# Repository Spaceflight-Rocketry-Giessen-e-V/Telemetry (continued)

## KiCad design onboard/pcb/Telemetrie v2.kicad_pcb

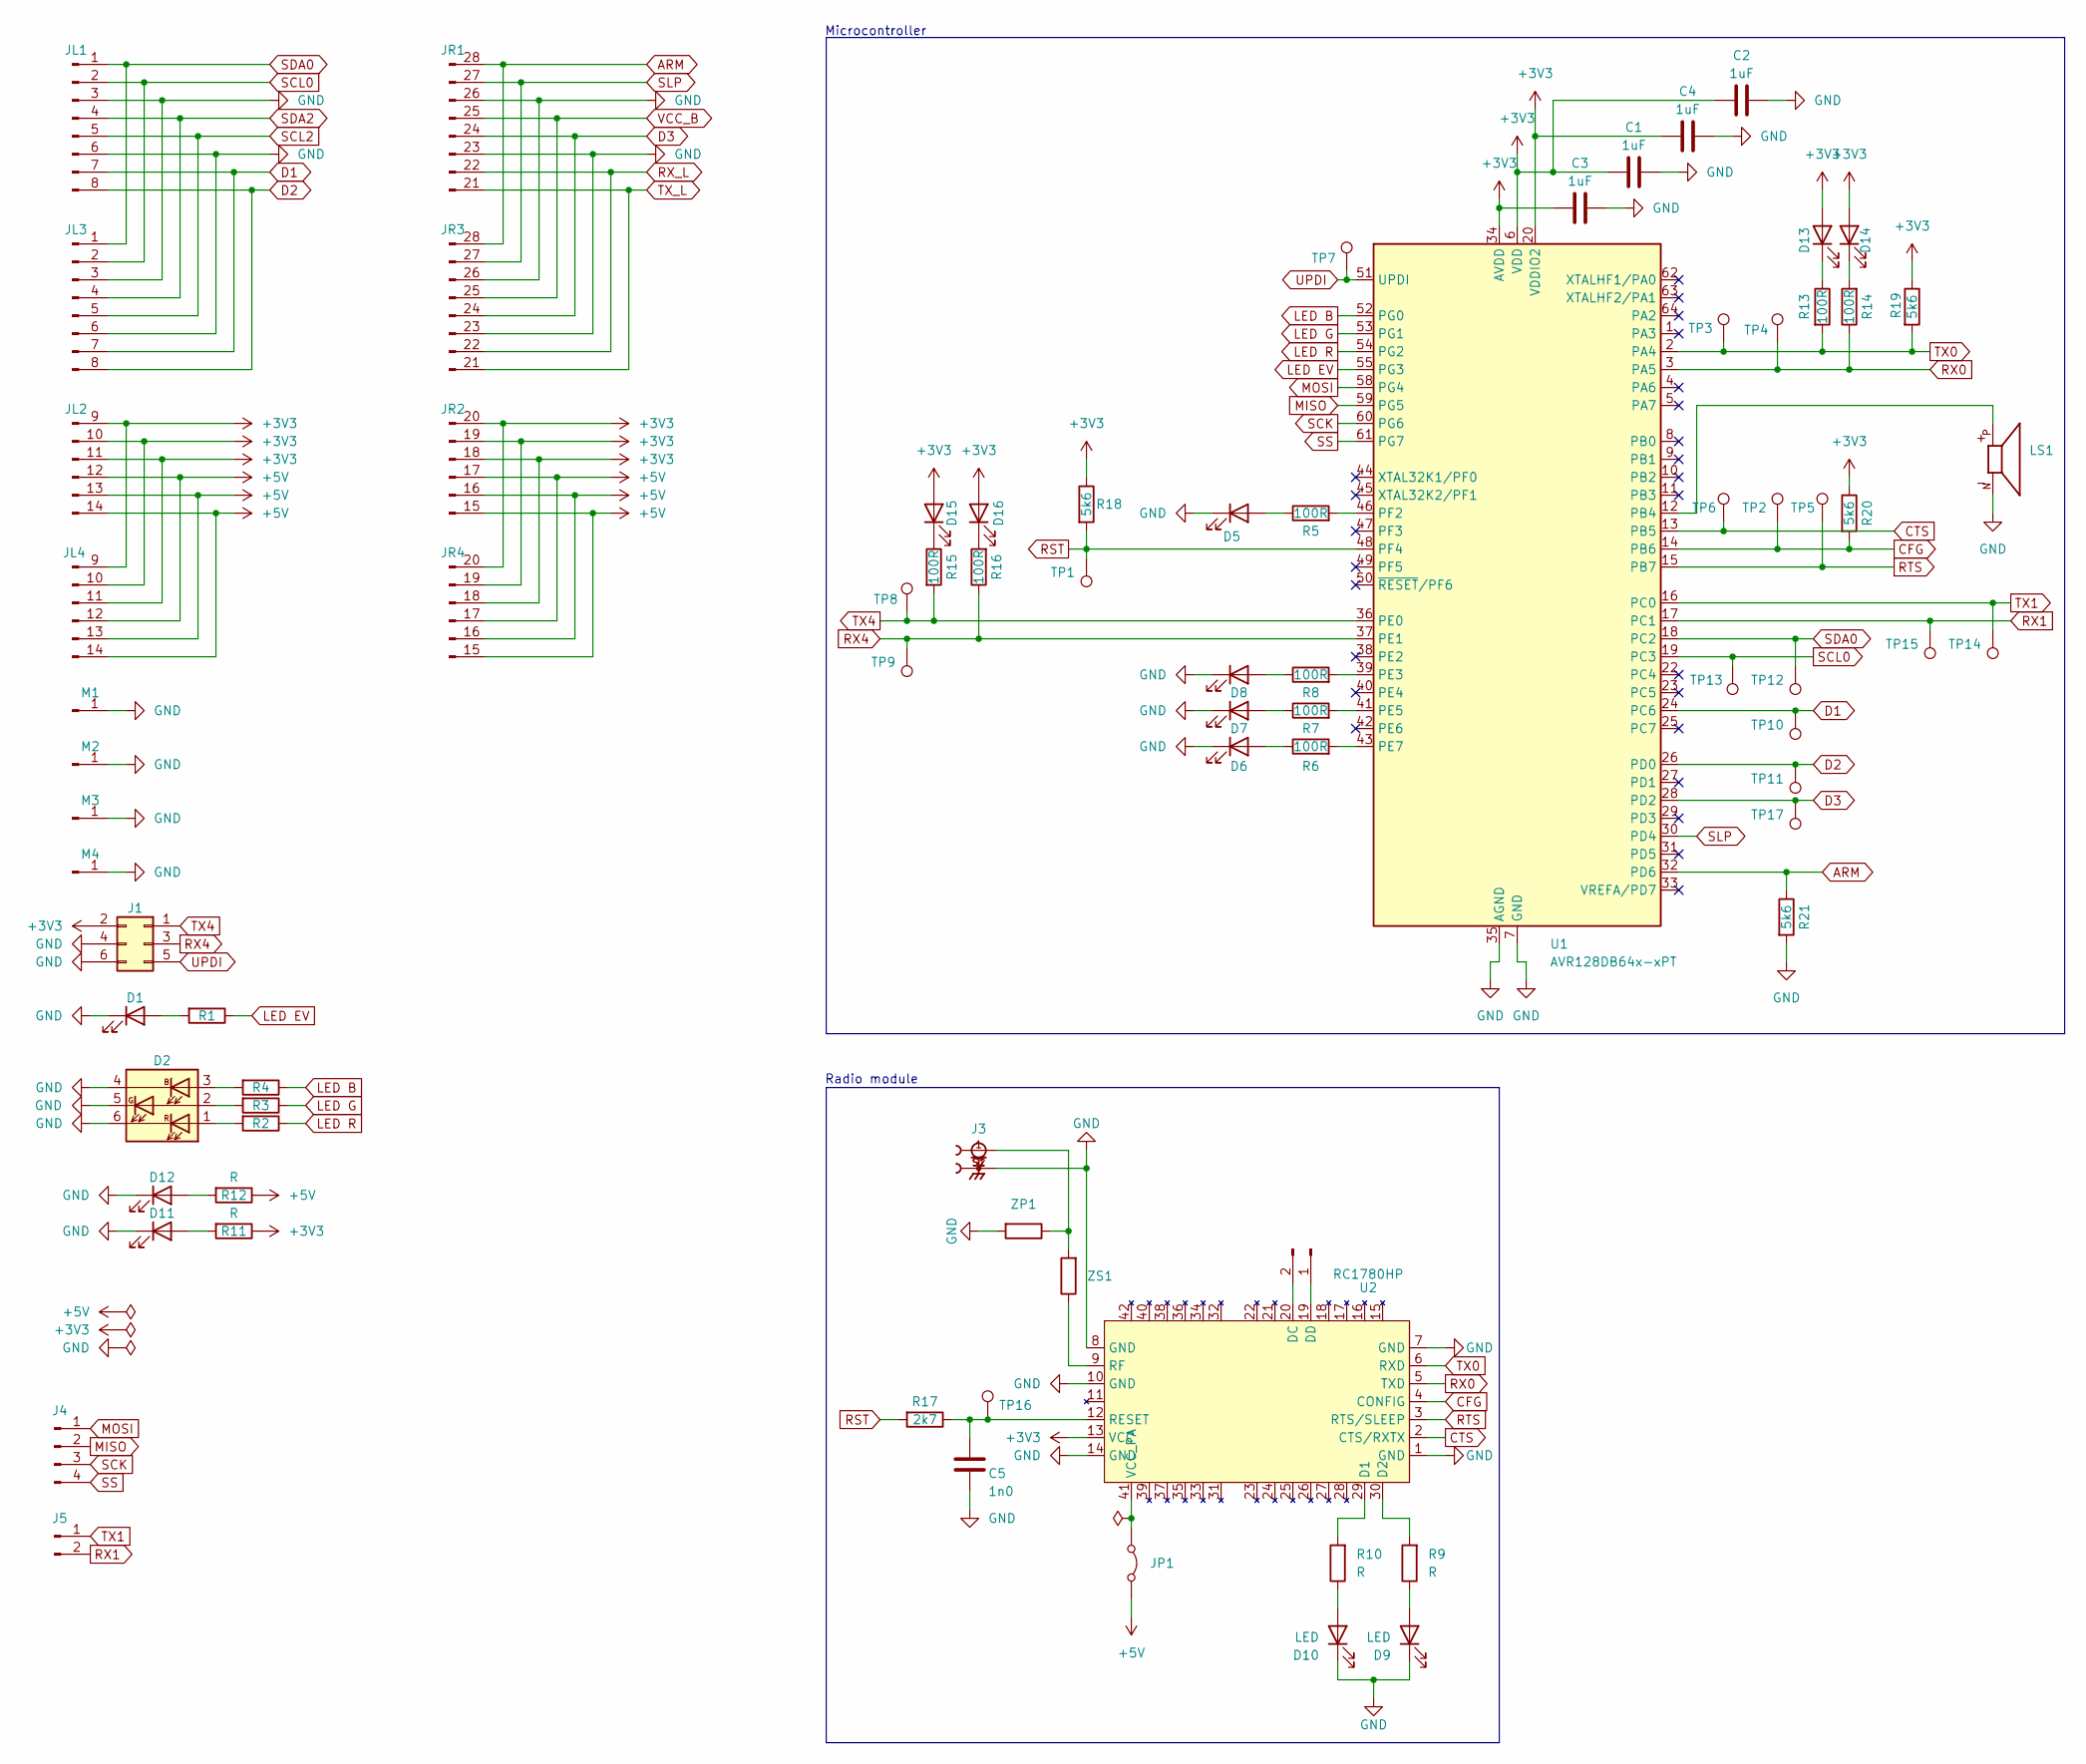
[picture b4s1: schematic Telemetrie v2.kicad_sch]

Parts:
C1, C2, C3, C4: 1uF; C_0805_2012Metric_Pad1.18x1.45mm_HandSolder
C5: 1n0; C_0805_2012Metric_Pad1.18x1.45mm_HandSolder
D1, D5, D6, D7, D8, D9, D10, D11, D12, D13, D14, D15, D16: LED; LED_0805_2012Metric_Pad1.15x1.40mm_HandSolder
D2: CLS6B-FKW; LED_RGB_Cree-PLCC-6_6x5mm_P2.1mm
J1: Conn_02x03_Odd_Even; PinSocket_2x03_P2.54mm_Horizontal
J2, J5: Conn_01x02_Pin; PinSocket_1x02_P2.54mm_Vertical
J3: SMA SMD; SMA Connector CONSMA001-SMD-G-T
J4: Conn_01x04_Pin; PinSocket_1x04_P2.54mm_Vertical
JL1, JL3: Conn_01x08_Pin; PinSocket_1x08_P2.54mm_Vertical
JL2, JL4: Conn_01x06_Pin; PinSocket_1x06_P2.54mm_Vertical
JP1: Jumper_2_Bridged; Solder Jumper
JR1, JR3: Conn_01x08_Pin; PinSocket_1x08_P2.54mm_Vertical
JR2, JR4: Conn_01x06_Pin; PinSocket_1x06_P2.54mm_Vertical
LS1: CMT-0525-75-SMT-TR; Buzzer XDCR_CMT-0525-75-SMT-TR; PARTREV 1.0
M1, M2, M3, M4: Conn_01x01_Pin; M4 Mounting Hole
R1, R2, R3, R4, R9, R10, R11, R12: R; R_0805_2012Metric_Pad1.20x1.40mm_HandSolder
R5, R6, R7, R8, R13, R14, R15, R16: 100R; R_0805_2012Metric_Pad1.20x1.40mm_HandSolder
R17: 2k7; R_0805_2012Metric_Pad1.20x1.40mm_HandSolder
R18, R19, R20, R21: 5k6; R_0805_2012Metric_Pad1.20x1.40mm_HandSolder
TP1, TP2, TP3, TP4, TP5, TP6, TP7, TP8, TP9, TP10, TP11, TP12, TP13, TP14, TP15, TP16, TP17: Test Point
U1: AVR128DB64x-xPT; TQFP-64_10x10mm_P0.5mm
U2: RC1780HP; Radiocrafts RC1780HP-RC232
ZP1: R; R_0805_2012Metric_Pad1.20x1.40mm_HandSolder
ZS1: R; R_0805_2012Metric_Pad1.20x1.40mm_HandSolder

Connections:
+3V3: C1.1, C2.2, C3.1, C4.2, D13.2 (A), D14.2 (A), D15.2 (A), D16.2 (A), J1.2, JL2.9 (Pin_1), JL2.10 (Pin_2), JL2.11 (Pin_3), JL4.9 (Pin_1), JL4.10 (Pin_2), JL4.11 (Pin_3), JR2.18 (Pin_3), JR2.19 (Pin_2), JR2.20 (Pin_1), JR4.18 (Pin_3), JR4.19 (Pin_2), JR4.20 (Pin_1), R11.1, R18.1, R19.1, R20.1, U1.6 (VDD), U1.20 (VDDIO2), U1.34 (AVDD), U1.56 (VDD), U2.13 (VCC)
+5V: JL2.12 (Pin_4), JL2.13 (Pin_5), JL2.14 (Pin_6), JL4.12 (Pin_4), JL4.13 (Pin_5), JL4.14 (Pin_6), JP1.2 (B), JR2.15 (Pin_6), JR2.16 (Pin_5), JR2.17 (Pin_4), JR4.15 (Pin_6), JR4.16 (Pin_5), JR4.17 (Pin_4), R12.1
ARM: JR1.28 (Pin_1), JR3.28 (Pin_1), R21.1, U1.32 (PD6)
CFG: R20.2, TP2.1, U1.14 (PB6), U2.4 (CONFIG)
CTS: TP6.1, U1.13 (PB5), U2.2 (CTS/RXTX)
D1: JL1.7, JL3.7, TP10.1, U1.24 (PC6)
D2: JL1.8, JL3.8, TP11.1, U1.26 (PD0)
D3: JR1.24 (Pin_5), JR3.24 (Pin_5), TP17.1, U1.28 (PD2)
GND: C1.2, C2.1, C3.2, C4.1, C5.2, D1.1 (K), D2.4 (KB), D2.5 (KR), D2.6 (KR), D5.1 (K), D6.1 (K), D7.1 (K), D8.1 (K), D9.1 (K), D10.1 (K), D11.1 (K), D12.1 (K), J1.4, J1.6, J3.S1, J3.S2, JL1.3, JL1.6, JL3.3, JL3.6, JR1.23 (Pin_6), JR1.26 (Pin_3), JR3.23 (Pin_6), JR3.26 (Pin_3), LS1.N, M1.1, M2.1, M3.1, M4.1, R21.2, U1.7 (GND), U1.21 (GND), U1.35 (AGND), U1.57 (GND), U2.1 (GND), U2.7 (GND), U2.8 (GND), U2.10 (GND), U2.14 (GND), ZP1.2
LED B: R4.1, U1.52 (PG0)
LED EV: R1.1, U1.55 (PG3)
LED G: R3.1, U1.53 (PG1)
LED R: R2.1, U1.54 (PG2)
MISO: J4.2, U1.59 (PG5)
MOSI: J4.1, U1.58 (PG4)
unnamed: D1.2 (A), R1.2
unnamed: D2.3 (AB), R4.2
unnamed: D2.2 (AG), R3.2
unnamed: D2.1 (AR), R2.2
unnamed: D5.2 (A), R5.1
unnamed: D6.2 (A), R6.1
unnamed: D7.2 (A), R7.1
unnamed: D8.2 (A), R8.1
unnamed: D9.2 (A), R9.1
unnamed: D10.2 (A), R10.1
unnamed: D11.2 (A), R11.2
unnamed: D12.2 (A), R12.2
unnamed: D13.1 (K), R13.1
unnamed: D14.1 (K), R14.2
unnamed: D15.1 (K), R15.1
unnamed: D16.1 (K), R16.2
unnamed: J2.1, U2.19 (DD)
unnamed: J2.2, U2.20 (DC)
unnamed: J3.1, ZP1.1, ZS1.2
unnamed: JP1.1 (A), U2.41 (VCC_PA)
unnamed: LS1.P, U1.12 (PB4)
unnamed: R8.2, U1.39 (PE3)
unnamed: R7.2, U1.41 (PE5)
unnamed: R6.2, U1.43 (PE7)
unnamed: R5.2, U1.46 (PF2)
unnamed: R10.2, U2.29 (D1)
unnamed: R9.2, U2.30 (D2)
unnamed: C5.1, R17.1, TP16.1, U2.12 (RESET)
unnamed: U2.9 (RF), ZS1.1
RST: R17.2, R18.2, TP1.1, U1.48 (PF4)
RTS: TP5.1, U1.15 (PB7), U2.3 (RTS/SLEEP)
RX0: R14.1, TP4.1, U1.3 (PA5), U2.5 (TXD)
RX1: J5.2, TP15.1, U1.17 (PC1)
RX4: J1.3, R16.1, TP9.1, U1.37 (PE1)
RX_L: JR1.22 (Pin_7), JR3.22 (Pin_7)
SCK: J4.3, U1.60 (PG6)
SCL0: JL1.2, JL3.2, TP13.1, U1.19 (PC3)
SCL2: JL1.5, JL3.5
SDA0: JL1.1, JL3.1, TP12.1, U1.18 (PC2)
SDA2: JL1.4, JL3.4
SLP: JR1.27 (Pin_2), JR3.27 (Pin_2), U1.30 (PD4)
SS: J4.4, U1.61 (PG7)
TX0: R13.2, R19.2, TP3.1, U1.2 (PA4), U2.6 (RXD)
TX1: J5.1, TP14.1, U1.16 (PC0)
TX4: J1.1, R15.2, TP8.1, U1.36 (PE0)
TX_L: JR1.21 (Pin_8), JR3.21 (Pin_8)
UPDI: J1.5, TP7.1, U1.51 (UPDI)
VCC_B: JR1.25 (Pin_4), JR3.25 (Pin_4)

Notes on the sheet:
Microcontroller
Radio module

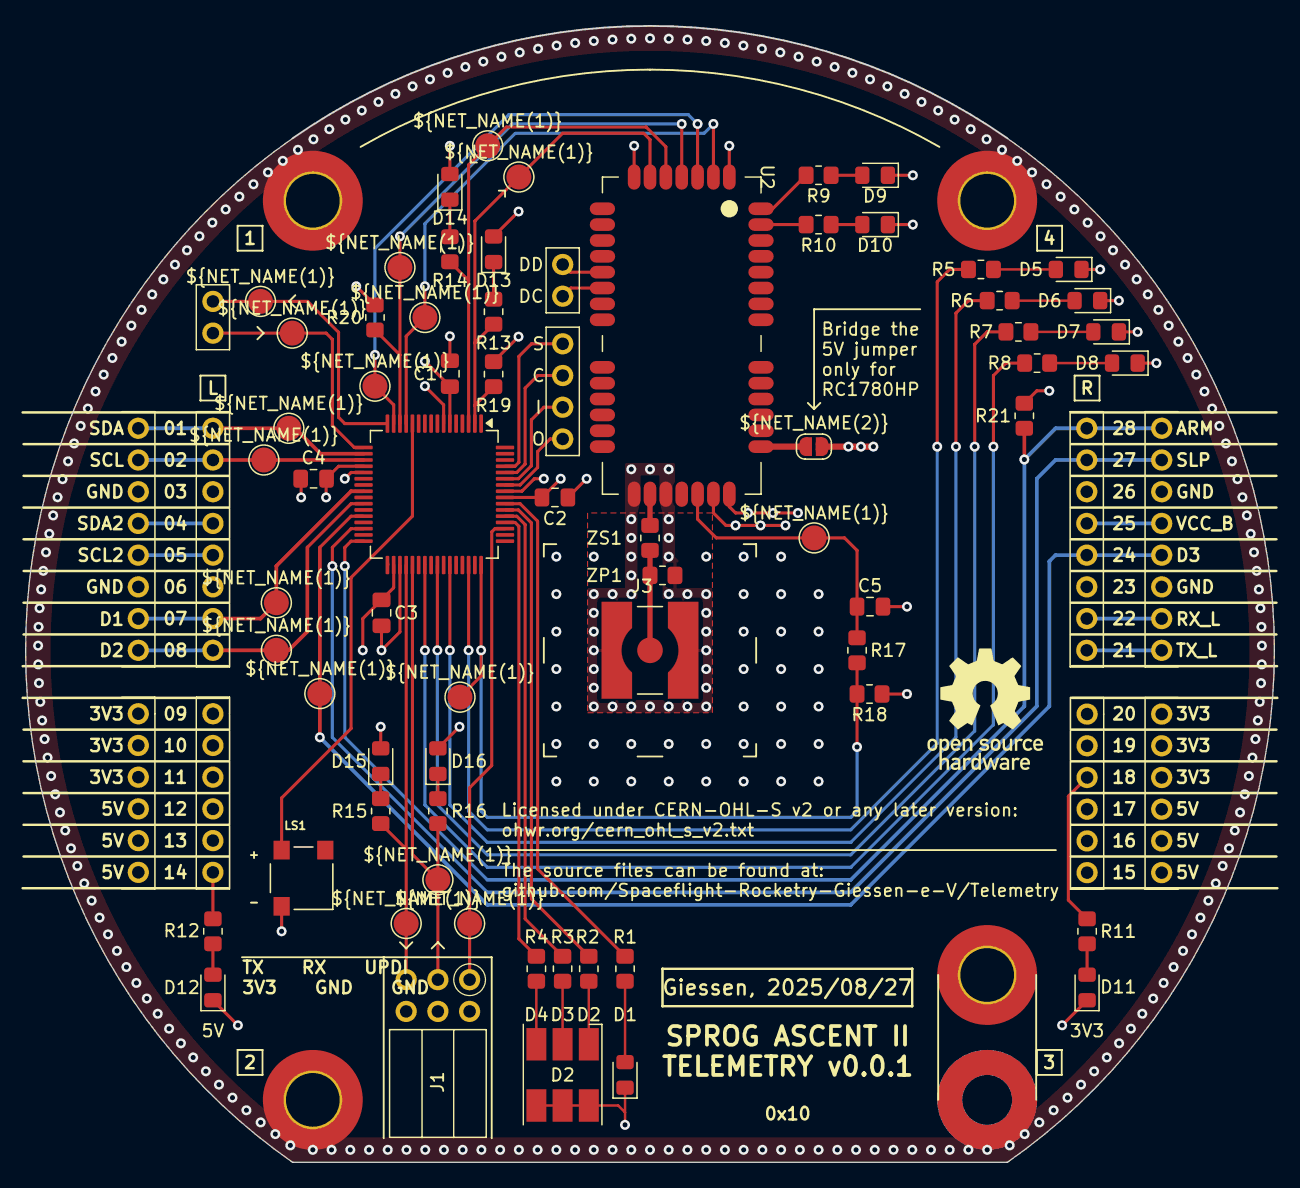
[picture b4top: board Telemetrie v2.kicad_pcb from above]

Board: 4 copper layers, 100.0 x 91.0 mm, 80 parts (0 on the bottom side), 63 nets.

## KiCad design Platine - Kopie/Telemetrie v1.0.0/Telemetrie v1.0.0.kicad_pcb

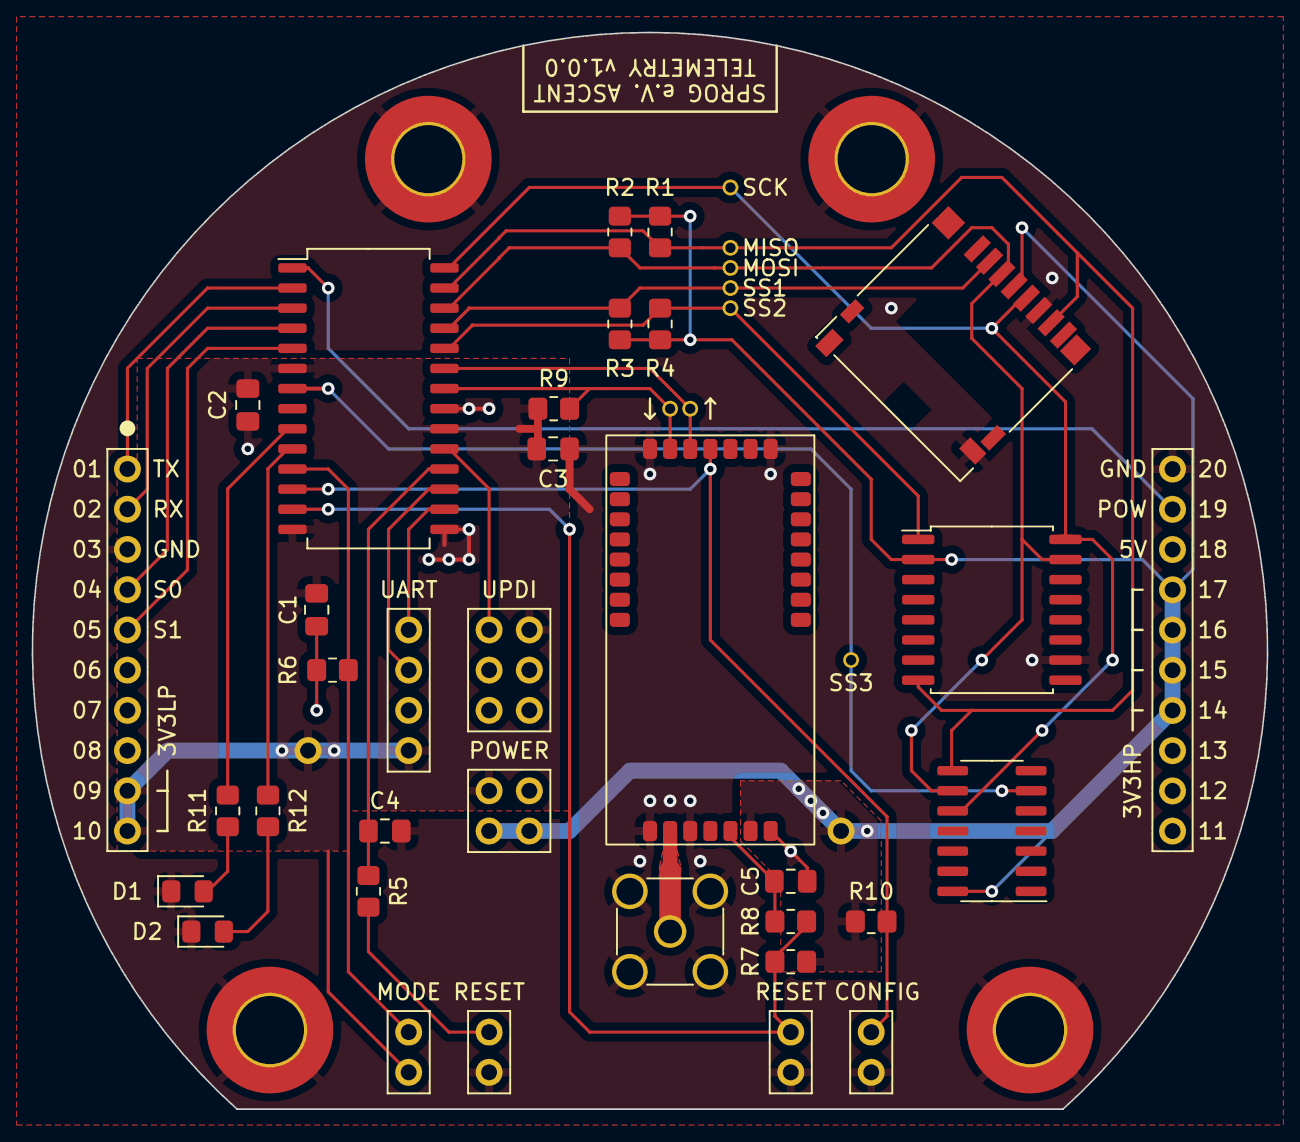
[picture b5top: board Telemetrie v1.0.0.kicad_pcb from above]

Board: 2 copper layers, 78.0 x 68.0 mm, 34 parts (0 on the bottom side), 30 nets.

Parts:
AE1: Antenna_Shield; SMA_Amphenol_901-144_Vertical
C1, C2, C3, C4: 1uF; C_0805_2012Metric_Pad1.18x1.45mm_HandSolder
C5: 1nF; C_0805_2012Metric_Pad1.18x1.45mm_HandSolder
D1, D2: LED; LED_0805_2012Metric_Pad1.15x1.40mm_HandSolder
J1: Micro_SD_Card; microSD_HC_Hirose_DM3D-SF
J2, J3: Conn_01x10; PinHeader_1x10_P2.54mm_Vertical
J4: UPDI_Conn; PinHeader_2x03_P2.54mm_Vertical
J5: Conn_USB; PinHeader_1x04_P2.54mm_Vertical
J8: Conn_02x02_Odd_Even; PinHeader_2x02_P2.54mm_Vertical
M1: RC1180HP; RC1180 only reflow
R1, R2, R3, R4, R6, R10: 4k7; R_0805_2012Metric_Pad1.20x1.40mm_HandSolder
R5: 330R; R_0805_2012Metric_Pad1.20x1.40mm_HandSolder
R7, R9: 5k6; R_0805_2012Metric_Pad1.20x1.40mm_HandSolder
R8: 2k7; R_0805_2012Metric_Pad1.20x1.40mm_HandSolder
R11, R12: 100R; R_0805_2012Metric_Pad1.20x1.40mm_HandSolder
RTC_SMD_SSOP-1: SOIC-14_3.9x8.7mm_P1.27mm
SW1, SW4: SW_DIP_x01; PinHeader_1x02_P2.54mm_Vertical
SW2, SW3: PinHeader_1x02_P2.54mm_Vertical
U1: AVR128DA28; SOIC-28W_7.5x18.7mm_P1.27mm
U2: SOIC-16W_7.5x10.3mm_P1.27mm

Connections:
+3.3V: J1.4 (VDD), J3.4, J3.5, J3.6, J3.7, J8.3, J8.4, M1.13 (VCC), R1.1, R2.1, R3.1, R4.1, R7.2, R10.2, RTC_SMD_SSOP-1.14 (Vcc), U2.2 (VCC)
+3V3: C1.2, C2.2, C3.1, J2.9, J2.10, J4.2, J5.1, J8.1, R9.1, SW1.2, U1.6 (VDDIO2), U1.14 (VDD), U1.20 (VDD)
CFG: M1.4 (CONFIG), R10.1, SW4.2, U1.12 (PD6)
GND: AE1.2 (Shield), C1.1, C2.1, C3.2, C4.2, C5.2, D1.1 (K), D2.1 (K), J1.6 (VSS), J1.9 (SHIELD), J2.3, J3.1, J4.6, J5.2, J8.2, M1.1 (GND), M1.7 (GND), M1.8 (GND), M1.10 (GND), M1.14 (GND), R6.2, SW2.1, SW3.1, SW4.1, U1.15 (GND), U1.21 (GND), U2.10 (GND)
MISO0: J1.7 (DAT0), R1.2, RTC_SMD_SSOP-1.8 (SO), U1.27 (PA5), U2.8 (IO1)
MODE: R6.1, SW1.1, U1.11 (PD5)
MOSI0: J1.3 (CMD), R2.2, RTC_SMD_SSOP-1.9 (SI), U1.26 (PA4), U2.15 (IO0)
unnamed: AE1.1 (A), M1.9 (RF)
unnamed: D1.2 (A), R11.1
unnamed: D2.2 (A), R12.1
unnamed: C5.1, M1.12 (RESET), R8.1
unnamed: R5.2, SW2.2
unnamed: R11.2, U1.9 (PD3)
unnamed: R12.2, U1.10 (PD4)
unnamed: C4.1, R5.1, U1.18 (PF6)
POW: J3.2, U1.1 (PA7)
RST: R7.1, R8.2, SW3.2, U1.13 (PD7)
RXD0: M1.5 (TXD), U1.23 (PA1)
RXD1: J2.2, U1.3 (PC1)
RXD2: J5.3, U1.17 (PF1)
S1: J2.4, U1.4 (PC2)
S2: J2.5, U1.5 (PC3)
SCK0: J1.5 (CLK), RTC_SMD_SSOP-1.10 (SCK), U1.28 (PA6), U2.16 (CLK)
SS1: J1.2 (DAT3/CD), R3.2, U1.25 (PA3)
SS2: R4.2, U1.24 (PA2), U2.1 (CS)
SS3: RTC_SMD_SSOP-1.6 (CS), U1.7 (PD1)
TXD0: M1.6 (RXD), R9.2, U1.22 (PA0)
TXD1: J2.1, U1.2 (PC0)
TXD2: J5.4, U1.16 (PF0)
UPDI: J4.1, U1.19 (UPDI)

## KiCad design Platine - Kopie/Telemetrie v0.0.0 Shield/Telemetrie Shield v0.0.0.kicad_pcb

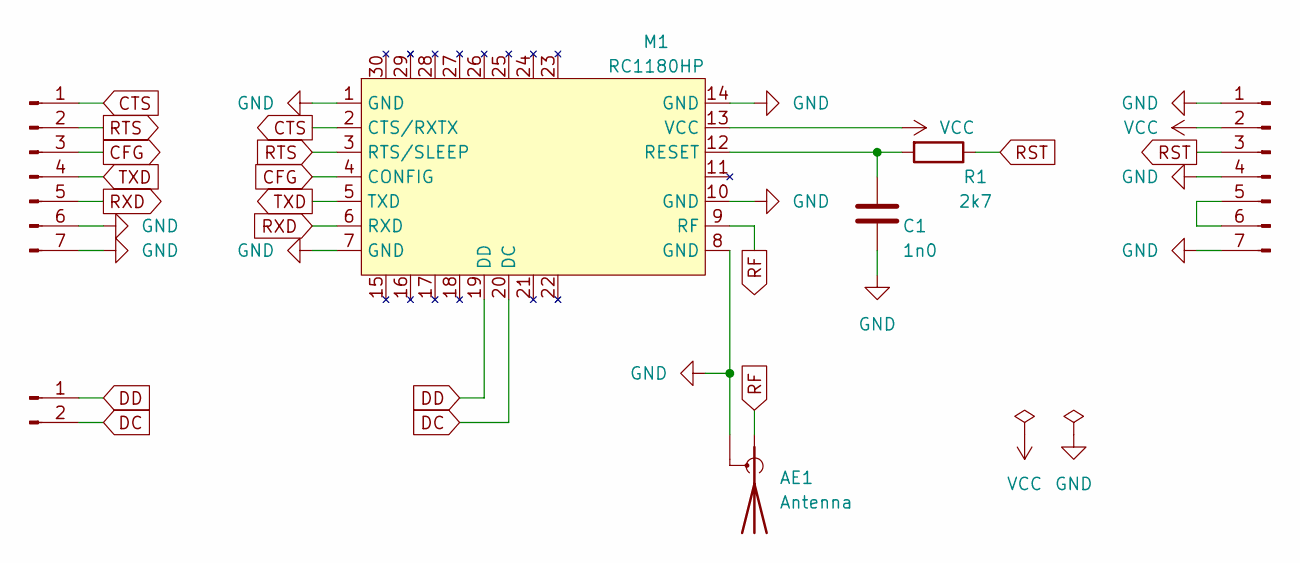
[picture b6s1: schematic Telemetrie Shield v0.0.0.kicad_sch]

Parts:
AE1: Antenna; SMA_Amphenol_901-144_Vertical
C1: 1n0; C_0805_2012Metric_Pad1.18x1.45mm_HandSolder
J1, J2: Conn_01x07_Pin; PinHeader_1x07_P2.54mm_Vertical
J3: Conn_01x02_Pin; double_pad
M1: RC1180HP; RC1180 only reflow
R1: 2k7; R_0805_2012Metric_Pad1.20x1.40mm_HandSolder

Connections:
CFG: J1.3, M1.4 (CONFIG)
CTS: J1.1, M1.2 (CTS/RXTX)
DC: J3.2, M1.20 (DC)
DD: J3.1, M1.19 (DD)
GND: AE1.2 (Shield), C1.2, J1.6, J1.7, J2.1, J2.4, J2.7, M1.1 (GND), M1.7 (GND), M1.8 (GND), M1.10 (GND), M1.14 (GND)
unnamed: J2.5, J2.6
unnamed: C1.1, M1.12 (RESET), R1.2
RF: AE1.1 (A), M1.9 (RF)
RST: J2.3, R1.1
RTS: J1.2, M1.3 (RTS/SLEEP)
RXD: J1.5, M1.6 (RXD)
TXD: J1.4, M1.5 (TXD)
VCC: J2.2, M1.13 (VCC)

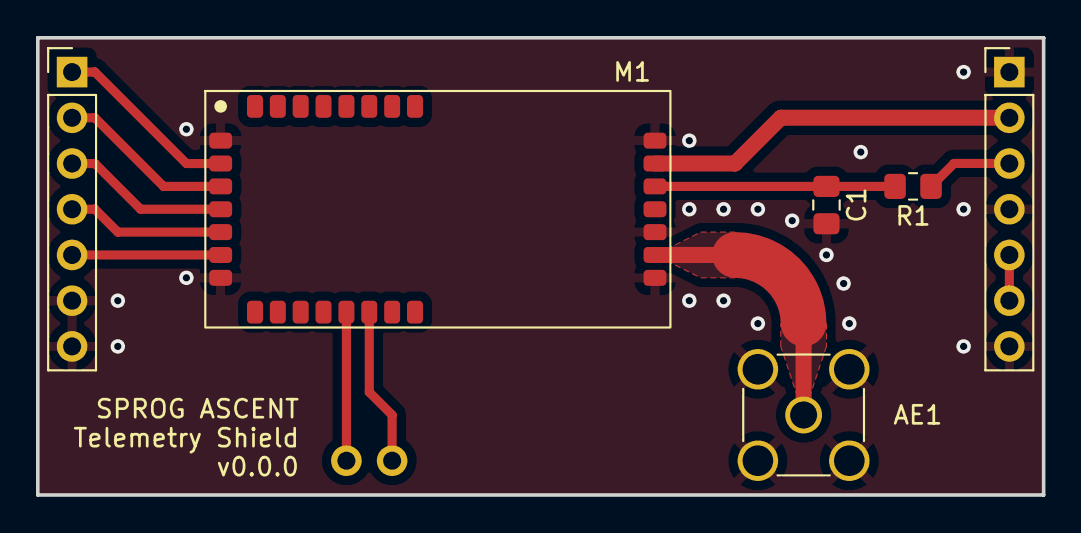
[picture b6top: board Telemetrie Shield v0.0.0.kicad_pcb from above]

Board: 2 copper layers, 55.9 x 25.4 mm, 7 parts (0 on the bottom side), 13 nets.

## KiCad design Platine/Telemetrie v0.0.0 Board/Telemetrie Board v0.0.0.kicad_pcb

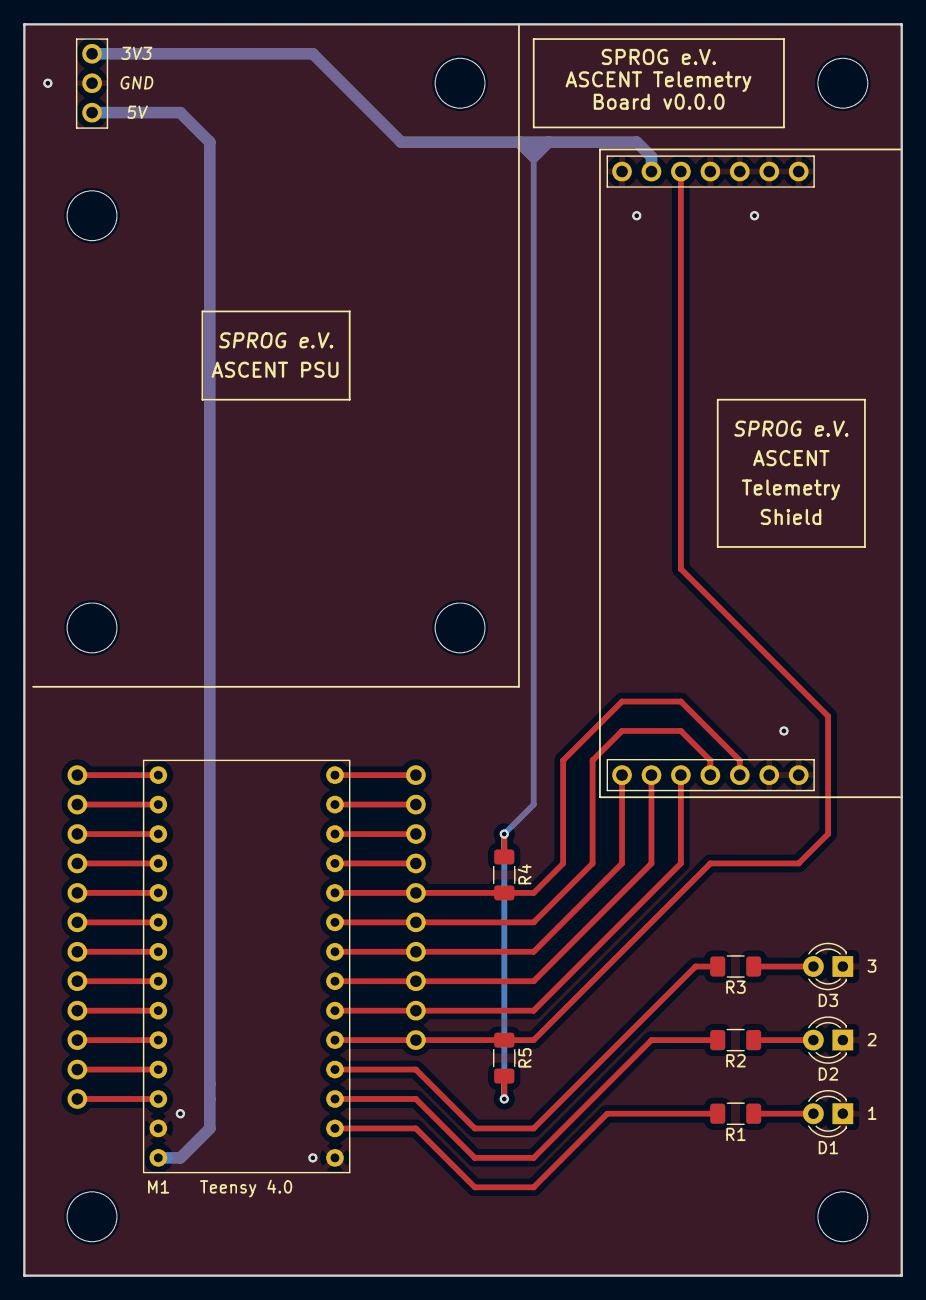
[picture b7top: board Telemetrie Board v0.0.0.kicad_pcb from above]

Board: 2 copper layers, 75.7 x 108.0 mm, 14 parts (0 on the bottom side), 31 nets.

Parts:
D1, D2, D3: LED; LED_D3.0mm
J2: Conn_01x12_Pin; pad_12
J3: Conn_01x04_Pin; pad_4
J5: Conn_01x03_Pin; PinSocket_1x03_P2.54mm_Vertical
J6, J7: Conn_01x07_Pin; PinSocket_1x07_P2.54mm_Vertical
M1: Teensy_4.0
R1, R2, R3: 150R; R_1206_3216Metric_Pad1.30x1.75mm_HandSolder
R4, R5: 5k6; R_1206_3216Metric_Pad1.30x1.75mm_HandSolder

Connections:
+3.3V: J5.1, J6.2, R4.1, R5.2
+5V: J5.3, M1.26 (Vin)
CFG: J7.3, M1.4 (D4)
CTS: J7.1, M1.6 (D6)
GND: D1.1 (K), D2.1 (K), D3.1 (K), J5.2, J6.1, J6.4, J6.5, J6.6, J6.7, J7.6, J7.7, M1.25 (GND), M1.27 (GND)
unnamed: D1.2 (A), R1.1
unnamed: D2.2 (A), R2.1
unnamed: D3.2 (A), R3.1
unnamed: J2.1, M1.24 (3.3V)
unnamed: J2.2, M1.23 (D23/A9)
unnamed: J2.3, M1.22 (D22/A8)
unnamed: J2.4, M1.21 (D21/A7)
unnamed: J2.5, M1.20 (D20/A6)
unnamed: J2.6, M1.19 (D19/A5)
unnamed: J2.7, M1.18 (D18/A4)
unnamed: J2.8, M1.17 (D17/A3)
unnamed: J2.9, M1.16 (D16/A2)
unnamed: J2.10, M1.15 (D15/A1)
unnamed: J2.11, M1.14 (D14/A0)
unnamed: J2.12, M1.13 (D13/LED)
unnamed: J3.1, M1.9 (D9)
unnamed: J3.2, M1.10 (D10)
unnamed: J3.3, M1.11 (D11)
unnamed: J3.4, M1.12 (D12)
unnamed: M1.0 (D0), R1.2
unnamed: M1.1 (D1), R2.2
unnamed: M1.2 (D2), R3.2
RST: J6.3, M1.3 (D3), R5.1
RTS: J7.2, M1.5 (D5)
RXD: J7.5, M1.8 (D8), R4.2
TXD: J7.4, M1.7 (D7)

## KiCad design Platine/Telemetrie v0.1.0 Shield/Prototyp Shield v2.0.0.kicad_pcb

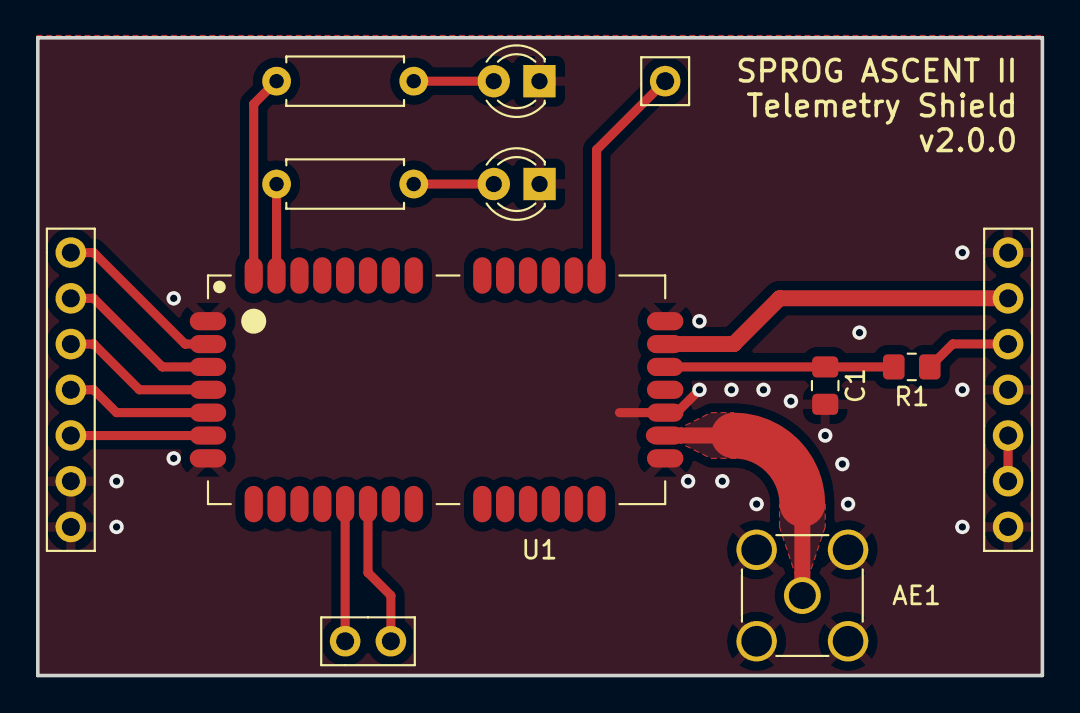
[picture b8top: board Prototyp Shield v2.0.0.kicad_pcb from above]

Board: 2 copper layers, 55.8 x 35.4 mm, 12 parts (0 on the bottom side), 18 nets.

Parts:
AE1: Antenna; SMA_Amphenol_901-144_Vertical
C1: 1n0; C_0805_2012Metric_Pad1.18x1.45mm_HandSolder
D1, D2: LED; LED_D3.0mm
J1, J2: Conn_01x07_Pin; PinHeader_1x07_P2.54mm_Vertical
J3: Conn_01x02_Pin; PinHeader_1x02_P2.54mm_Vertical
J4: Conn_01x01_Pin; PinHeader_1x01_P2.54mm_Vertical
R1: 2k7; R_0805_2012Metric_Pad1.20x1.40mm_HandSolder
R2, R3: R; R_Axial_DIN0207_L6.3mm_D2.5mm_P7.62mm_Horizontal
U1: RC1780HP

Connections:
CFG: J1.3, U1.4 (CONFIG)
CTS: J1.1, U1.2 (CTS/RXTX)
DC: J3.2, U1.20 (DC)
DD: J3.1, U1.19 (DD)
GND: AE1.2 (Shield), C1.2, D1.1 (K), D2.1 (K), J1.6, J1.7, J2.1, J2.4, J2.7, U1.1 (GND), U1.7 (GND), U1.8 (GND), U1.10 (GND), U1.14 (GND)
unnamed: D1.2 (A), R2.1
unnamed: D2.2 (A), R3.1
unnamed: J2.5, J2.6
unnamed: R2.2, U1.29 (D1)
unnamed: R3.2, U1.30 (D2)
unnamed: C1.1, R1.2, U1.12 (RESET)
RF: AE1.1 (A), U1.9 (RF)
RST: J2.3, R1.1
RTS: J1.2, U1.3 (RTS/SLEEP)
RXD: J1.5, U1.6 (RXD)
TXD: J1.4, U1.5 (TXD)
VCC: J2.2, U1.13 (VCC)
VCC_PA: J4.1, U1.41 (VCC_PA)

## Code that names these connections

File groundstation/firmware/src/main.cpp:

/*
    groundstation - main.cpp of the groundstation for the ASCENT III telemetry system.
    Spaceflight Rocketry Giessen e.V.
    Published under the CERN OHL-S v2 license at https://github.com/Spaceflight-Rocketry-Giessen-e-V/Telemetry.
*/

#include "header.h"
#include "utility.h"

// LED Pins Initialization

ledStruct pinLed;

// Button Pins Initialization

buttonStruct pinButton;

// Pin Declarations

uint8_t pinControlBox1 = PIN_PE7;
uint8_t pinControlBox2 = PIN_PE6;

// UART Declarations

HardwareSerial *SerialUSB1 = &Serial5;
HardwareSerial *SerialUSB2 = &Serial2;

uint8_t pinTX_USB1 = PIN_PG0;
uint8_t pinRX_USB1 = PIN_PG1;
uint8_t pinTX_USB2 = PIN_PF0;
uint8_t pinRX_USB2 = PIN_PF1;

// Initialize Radio Modules

// First D-Sub
RC17xxHP_RC232 rc1780hp(&Serial4, PIN_PE0, PIN_PE1, 19200, PIN_PE4, PIN_PE5, PIN_PE2, PIN_PE3);
// Second D-Sub
RC17xxHP_RC232 rc1701hp(&Serial1, PIN_PC0, PIN_PC1, 19200, PIN_PC4, PIN_PC5, PIN_PC2, PIN_PC3);

// Packet Declarations

Packet commandPacket;
Packet framePacket;
Packet flightDataPacket;
Packet telemetryDataPacket;

// 

dataStruct dataVars;

uint8_t packetBuffer[32];
uint8_t packetBufferIndex = 0;

void setup()
{
  pinLed.R = PIN_PG5;
  pinLed.G = PIN_PG4;
  pinLed.B = PIN_PG3;
  pinLed.D1 = PIN_PA0;
  pinLed.D2 = PIN_PG7;
  pinLed.D3 = PIN_PG6;
  pinLed.rssi_1 = PIN_PD7;
  pinLed.rssi_2 = PIN_PD6;
  pinLed.rssi_3 = PIN_PD5;
  pinLed.rssi_4 = PIN_PD4;
  pinLed.rssi_5 = PIN_PD3;
  pinLed.rssi_6 = PIN_PD2;
  pinLed.rssi_7 = PIN_PD1;
  pinLed.rssi_8 = PIN_PD0;

  pinLed.pinMode();

  pinButton.sw1 = PIN_PG2;
  pinButton.sw2 = PIN_PF6;
  pinButton.sw3 = PIN_PF5;
  pinButton.sw4 = PIN_PF4;
  pinButton.sw5 = PIN_PF3;
  pinButton.sw6 = PIN_PF2;

  pinButton.pinMode();

  pinMode(pinControlBox1, INPUT);
  pinMode(pinControlBox2, INPUT);

  ledUpdate(SETUPBEGIN, &pinLed); // R On

  // UART Declarations

  SerialUSB1->pins(pinTX_USB1, pinRX_USB1);
  SerialUSB2->pins(pinTX_USB2, pinRX_USB2);

  SerialUSB1->begin(115200);
  SerialUSB2->begin(115200);

  // Initialize I2C (Display)

  // Wire.pins(PIN_PC6, PIN_PC7);
  // Wire.begin();

  // Initialize Radio Modules

  radioModulesSetup(&rc1780hp, &rc1701hp, &pinLed);

  ledUpdate(SETUPRADIOMODULS, &pinLed); // B On

  // Packet Components Initializations

  commandPacket.addComponent(new parity_Component());
  commandPacket.addComponent(new char_Component(&dataVars.command));

  framePacket.addComponent(new cobs_Component(0xEE, 4));
  framePacket.addComponent(new parity_Component());
  framePacket.addComponent(new uint8_t_Component(&dataVars.packetIdentifier, 1, 0, 1));
  framePacket.addComponent(new empty_Component(18));
  framePacket.addComponent(new empty_Component(32));
  framePacket.addComponent(new empty_Component(32));
  framePacket.addComponent(new const_Component(0xEE, 8, 255));
  framePacket.addComponent(new float_Component(&dataVars.rssi, 8, 0.0f, -127.5f, 255));

  flightDataPacket.addComponent(new empty_Component(6));
  flightDataPacket.addComponent(new float_Component(&dataVars.acceleration, 10, -17, 17.1));
  flightDataPacket.addComponent(new float_Component(&dataVars.heightPressure, 15, 0, 6553.4));
  flightDataPacket.addComponent(new uint8_t_Component(&dataVars.flightEvents, 5, 0, 31));
  flightDataPacket.addComponent(new float_Component(&dataVars.latitude, 26, -90, 90));
  flightDataPacket.addComponent(new float_Component(&dataVars.longitude, 26, -180, 180));
  flightDataPacket.addComponent(new empty_Component(16));

  telemetryDataPacket.addComponent(new empty_Component(6));
  telemetryDataPacket.addComponent(new empty_Component(2));
  telemetryDataPacket.addComponent(new uint8_t_Component(&dataVars.stateTelemetry, 2, 0, 3));
  telemetryDataPacket.addComponent(new uint8_t_Component(&dataVars.stateControl, 2, 0, 3));
  telemetryDataPacket.addComponent(new uint8_t_Component(&dataVars.statePower, 2, 0, 3));
  telemetryDataPacket.addComponent(new uint8_t_Component(&dataVars.stateSens, 2, 0, 3));
  telemetryDataPacket.addComponent(new empty_Component(1));
  telemetryDataPacket.addComponent(new float_Component(&dataVars.heightGNSS, 15, 0, 6553.4));
  telemetryDataPacket.addComponent(new uint8_t_Component(&dataVars.satCountGNSS, 4, 0, 15));
  telemetryDataPacket.addComponent(new float_Component(&dataVars.hdopGNSS, 4, 0, 7.5));
  telemetryDataPacket.addComponent(new uint8_t_Component(&dataVars.temperatureElectronics, 4, 0, 150));
  telemetryDataPacket.addComponent(new uint8_t_Component(&dataVars.temperatureBattery, 4, 0, 150));
  telemetryDataPacket.addComponent(new uint8_t_Component(&dataVars.stateCapacitors, 4, 0, 15));
  telemetryDataPacket.addComponent(new uint8_t_Component(&dataVars.continuityPyros, 2, 0, 3));
  telemetryDataPacket.addComponent(new uint8_t_Component(&dataVars.pressureDecoupler, 1, 0, 1));
  telemetryDataPacket.addComponent(new uint8_t_Component(&dataVars.ldrDecoupler, 1, 0, 1));
  telemetryDataPacket.addComponent(new empty_Component(2));
  telemetryDataPacket.addComponent(new float_Component(&dataVars.voltageBattery, 6, 5, 8.15));
  telemetryDataPacket.addComponent(new float_Component(&dataVars.currentBattery, 3, 0, 1.75));
  telemetryDataPacket.addComponent(new float_Component(&dataVars.currentUmbilical, 3, 0, 1.75));
  telemetryDataPacket.addComponent(new uint8_t_Component(&dataVars.stateUmbilical, 1, 0, 1));
  telemetryDataPacket.addComponent(new uint8_t_Component(&dataVars.lowPowerMode, 1, 0, 1));
  telemetryDataPacket.addComponent(new float_Component(&dataVars.voltageBatteryCOTS, 5, 5, 11.2));
  telemetryDataPacket.addComponent(new empty_Component(11));
  telemetryDataPacket.addComponent(new empty_Component(16));

  // Setup Complete

  ledUpdate(SETUPEND, &pinLed); // G On
}

void loop()
{
  // Check both USBs for commands
  dataVars.command = commandReceive(SerialUSB1);
  commandExecute(&rc1701hp, dataVars.command, &commandPacket);
  dataVars.command = commandReceive(SerialUSB2);
  commandExecute(&rc1701hp, dataVars.command, &commandPacket);

  buttonCheck(pinButton);
  controlBoxCheck(pinControlBox1, pinControlBox2);

  if (packetReceive(&rc1780hp, packetBuffer, &packetBufferIndex, &dataVars, &framePacket, &flightDataPacket, &telemetryDataPacket) == 0)
  {
    dataSendUsb(SerialUSB1, &dataVars);
    dataSendUsb(SerialUSB2, &dataVars);

    displayUpdate(0x00, &dataVars);

    ledRssiUpdate(dataVars.rssi, &pinLed);
  }
}

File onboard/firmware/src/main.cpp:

/*
    onboard - main.cpp of the board computer for the ASCENT III telemetry system.
    Spaceflight Rocketry Giessen e.V.
    Published under the CERN OHL-S v2 license at https://github.com/Spaceflight-Rocketry-Giessen-e-V/Telemetry.
*/

#include "header.h"
#include "utility.h"

// LED Pins Initialization

ledStruct pinLed;

// Pin Declarations

uint8_t pinSLP = PIN_PG0;
uint8_t pinARM1 = PIN_PG1;
uint8_t pinD26 = PIN_PF4;
uint8_t pinD27 = PIN_PF5;
uint8_t pinD28 = PIN_PF6;
uint8_t pinD4 = PIN_PC6;
uint8_t pinD5 = PIN_PC7;
uint8_t pinBuzzer = PIN_PB0;

// UART Declarations

HardwareSerial *SerialUSB = &Serial4;
HardwareSerial *SerialUmbilical = &Serial1;

uint8_t pinTX_USB = PIN_PE4;
uint8_t pinRX_USB = PIN_PE5;
uint8_t pinTX_Umbilical = PIN_PC0;
uint8_t pinRX_Umbilical = PIN_PC1;

// Initialize Radio Modules

RC17xxHP_RC232 rc1780hp(&Serial0, PIN_PA0, PIN_PA1, 19200, PIN_PA5, PIN_PG7, PIN_PA3, PIN_PA4);
RC17xxHP_RC232 rc1701hp(&Serial3, PIN_PB4, PIN_PB5, 19200, PIN_PB3, PIN_PG6, PIN_PB1, PIN_PB2);
dataStruct dataVars;

// Data Arrays Preparations

const uint8_t uint8CountPower = 3;
uint8_t *uint8ListPower[uint8CountPower] = {&dataVars.statePower, &dataVars.stateUmbilical, &dataVars.temperatureBattery};
const uint8_t floatCountPower = 4;
float *floatListPower[floatCountPower] = {&dataVars.currentUmbilical, &dataVars.currentBattery, &dataVars.voltageBattery, &dataVars.voltageBatteryCOTS};

const uint8_t uint8CountSens = 3;
uint8_t *uint8ListSens[uint8CountSens] = {&dataVars.stateSens, &dataVars.satCountGNSS, &dataVars.temperatureElectronics};
const uint8_t floatCountSens = 6;
float *floatListSens[floatCountSens] = {&dataVars.latitude, &dataVars.longitude, &dataVars.heightPressure, &dataVars.acceleration, &dataVars.heightGNSS, &dataVars.hdopGNSS};

const uint8_t uint8CountControl = 6;
uint8_t *uint8ListControl[uint8CountControl] = {&dataVars.stateControl, &dataVars.flightEvents, &dataVars.stateCapacitors, &dataVars.pressureDecoupler, &dataVars.ldrDecoupler, &dataVars.continuityPyros};
const uint8_t floatCountControl = 0;
float *floatListControl[floatCountControl] = {};

// Subsystems Initialization

Subsystem subsystemPower(0x50, &pinLed.Power, &dataVars.statePower, uint8ListPower, uint8CountPower, floatListPower, floatCountPower);
Subsystem subsystemSens(0x20, &pinLed.Sens, &dataVars.stateSens, uint8ListSens, uint8CountSens, floatListSens, floatCountSens);
Subsystem subsystemControl(0x40, &pinLed.Control, &dataVars.stateControl, uint8ListControl, uint8CountControl, floatListControl, floatCountControl);

const uint8_t subsystemsCount = 3;
Subsystem *subsystemList[subsystemsCount] = {&subsystemSens, &subsystemPower, &subsystemControl};

// Packet Declarations

Packet commandPacket;
Packet flightDataPacket;
Packet telemetryDataPacket;

// Loop Variables Declaration

const uint8_t loopFrequency = 10;            // in Hz       10 Hz = 100 ms interval
const uint8_t timeBetweenStandbyPackets = 5; // in seconds. In standby, data packets aren't send every loop

uint8_t flightMode = 0;
uint32_t loopCount = 0;
uint32_t loopStartTime = 0;

void setup()
{
  pinLed.R = PIN_PF0;
  pinLed.G = PIN_PE7;
  pinLed.B = PIN_PE6;
  pinLed.D1 = PIN_PF3;
  pinLed.D2 = PIN_PF2;
  pinLed.D3 = PIN_PF1;
  pinLed.Debug1 = PIN_PB6;
  pinLed.Debug2 = PIN_PB7;
  pinLed.Power = PIN_PD3;
  pinLed.Sens = PIN_PD4;
  pinLed.Control = PIN_PD2;

  pinLed.lowPowerMode = new uint8_t(0);

  pinLed.pinMode();

  ledUpdate(SETUPBEGIN, &pinLed); // R On

  // Pin Initialisations

  pinMode(pinSLP, OUTPUT);
  pinMode(pinARM1, OUTPUT);
  pinMode(pinBuzzer, OUTPUT);

  digitalWrite(pinSLP, LOW);
  digitalWrite(pinARM1, LOW);

  // UART Declarations

  SerialUSB->pins(pinTX_USB, pinRX_USB);
  SerialUmbilical->pins(pinTX_Umbilical, pinRX_Umbilical);

  SerialUSB->begin(115200);
  SerialUmbilical->begin(115200);

  // Initialize I2C

  Wire.pins(PIN_PC2, PIN_PC3);
  Wire.begin();

  // Initialize Radio Modules

  radioModulesSetup(&rc1780hp, &rc1701hp, &pinLed, pinBuzzer);

  ledUpdate(SETUPRADIOMODULS, &pinLed); // B On

  // Packet Components Initializations

  commandPacket.addComponent(new parity_Component());
  commandPacket.addComponent(new char_Component(&dataVars.command));

  flightDataPacket.addComponent(new cobs_Component(0xEE, 4));
  flightDataPacket.addComponent(new parity_Component());
  flightDataPacket.addComponent(new const_Component(0, 1));
  flightDataPacket.addComponent(new float_Component(&dataVars.acceleration, 10, -17, 17.1));
  flightDataPacket.addComponent(new float_Component(&dataVars.heightPressure, 15, 0, 6553.4));
  flightDataPacket.addComponent(new uint8_t_Component(&dataVars.flightEvents, 5, 0, 31));
  flightDataPacket.addComponent(new float_Component(&dataVars.latitude, 26, -90, 90));
  flightDataPacket.addComponent(new float_Component(&dataVars.longitude, 26, -180, 180));
  flightDataPacket.addComponent(new const_Component(0xEE, 8, 255));

  telemetryDataPacket.addComponent(new cobs_Component(0xEE, 4));
  telemetryDataPacket.addComponent(new parity_Component());
  telemetryDataPacket.addComponent(new const_Component(1, 1));
  telemetryDataPacket.addComponent(new empty_Component(2));
  telemetryDataPacket.addComponent(new uint8_t_Component(&dataVars.stateTelemetry, 2, 0, 3));
  telemetryDataPacket.addComponent(new uint8_t_Component(&dataVars.stateControl, 2, 0, 3));
  telemetryDataPacket.addComponent(new uint8_t_Component(&dataVars.statePower, 2, 0, 3));
  telemetryDataPacket.addComponent(new uint8_t_Component(&dataVars.stateSens, 2, 0, 3));
  telemetryDataPacket.addComponent(new empty_Component(1));
  telemetryDataPacket.addComponent(new float_Component(&dataVars.heightGNSS, 15, 0, 6553.4));
  telemetryDataPacket.addComponent(new uint8_t_Component(&dataVars.satCountGNSS, 4, 0, 15));
  telemetryDataPacket.addComponent(new float_Component(&dataVars.hdopGNSS, 4, 0, 7.5));
  telemetryDataPacket.addComponent(new uint8_t_Component(&dataVars.temperatureElectronics, 4, 0, 150));
  telemetryDataPacket.addComponent(new uint8_t_Component(&dataVars.temperatureBattery, 4, 0, 150));
  telemetryDataPacket.addComponent(new uint8_t_Component(&dataVars.stateCapacitors, 4, 0, 15));
  telemetryDataPacket.addComponent(new uint8_t_Component(&dataVars.continuityPyros, 2, 0, 3));
  telemetryDataPacket.addComponent(new uint8_t_Component(&dataVars.pressureDecoupler, 1, 0, 1));
  telemetryDataPacket.addComponent(new uint8_t_Component(&dataVars.ldrDecoupler, 1, 0, 1));
  telemetryDataPacket.addComponent(new empty_Component(2));
  telemetryDataPacket.addComponent(new float_Component(&dataVars.voltageBattery, 6, 5, 8.15));
  telemetryDataPacket.addComponent(new float_Component(&dataVars.currentBattery, 3, 0, 1.75));
  telemetryDataPacket.addComponent(new float_Component(&dataVars.currentUmbilical, 3, 0, 1.75));
  telemetryDataPacket.addComponent(new uint8_t_Component(&dataVars.stateUmbilical, 1, 0, 1));
  telemetryDataPacket.addComponent(new uint8_t_Component(pinLed.lowPowerMode, 1, 0, 1));
  telemetryDataPacket.addComponent(new float_Component(&dataVars.voltageBatteryCOTS, 5, 5, 11.2));
  telemetryDataPacket.addComponent(new empty_Component(11));
  telemetryDataPacket.addComponent(new const_Component(0xEE, 8, 255));

  // Setup Complete

  buzzerSound(pinBuzzer);
  dataVars.stateTelemetry = 3;
  ledUpdate(SETUPEND, &pinLed); // G On
}

void loop()
{
  subsystemsConnCheck(subsystemList, subsystemsCount);
  subsystemsDataGet(subsystemList, subsystemsCount);
  subsystemsLedUpdate(subsystemList, subsystemsCount, *(pinLed.lowPowerMode));

  commandReceive(&rc1701hp, &commandPacket);
  commandExecute(dataVars.command, &rc1780hp, &dataVars, &pinLed, &flightMode, subsystemList, subsystemsCount, &subsystemSens, &subsystemControl, &flightDataPacket, &telemetryDataPacket, pinARM1, pinSLP);

  uint8_t packetType = packetSendCheck(&flightMode, loopFrequency, timeBetweenStandbyPackets, loopCount);
  packetSend(&rc1780hp, packetType, &flightDataPacket, &telemetryDataPacket);
  flashWrite(&dataVars);

  ledUpdate(UPDATE, &pinLed);

  loopVariablesUpdate(&loopCount, &loopStartTime, loopFrequency, pinLed.D1);
}
